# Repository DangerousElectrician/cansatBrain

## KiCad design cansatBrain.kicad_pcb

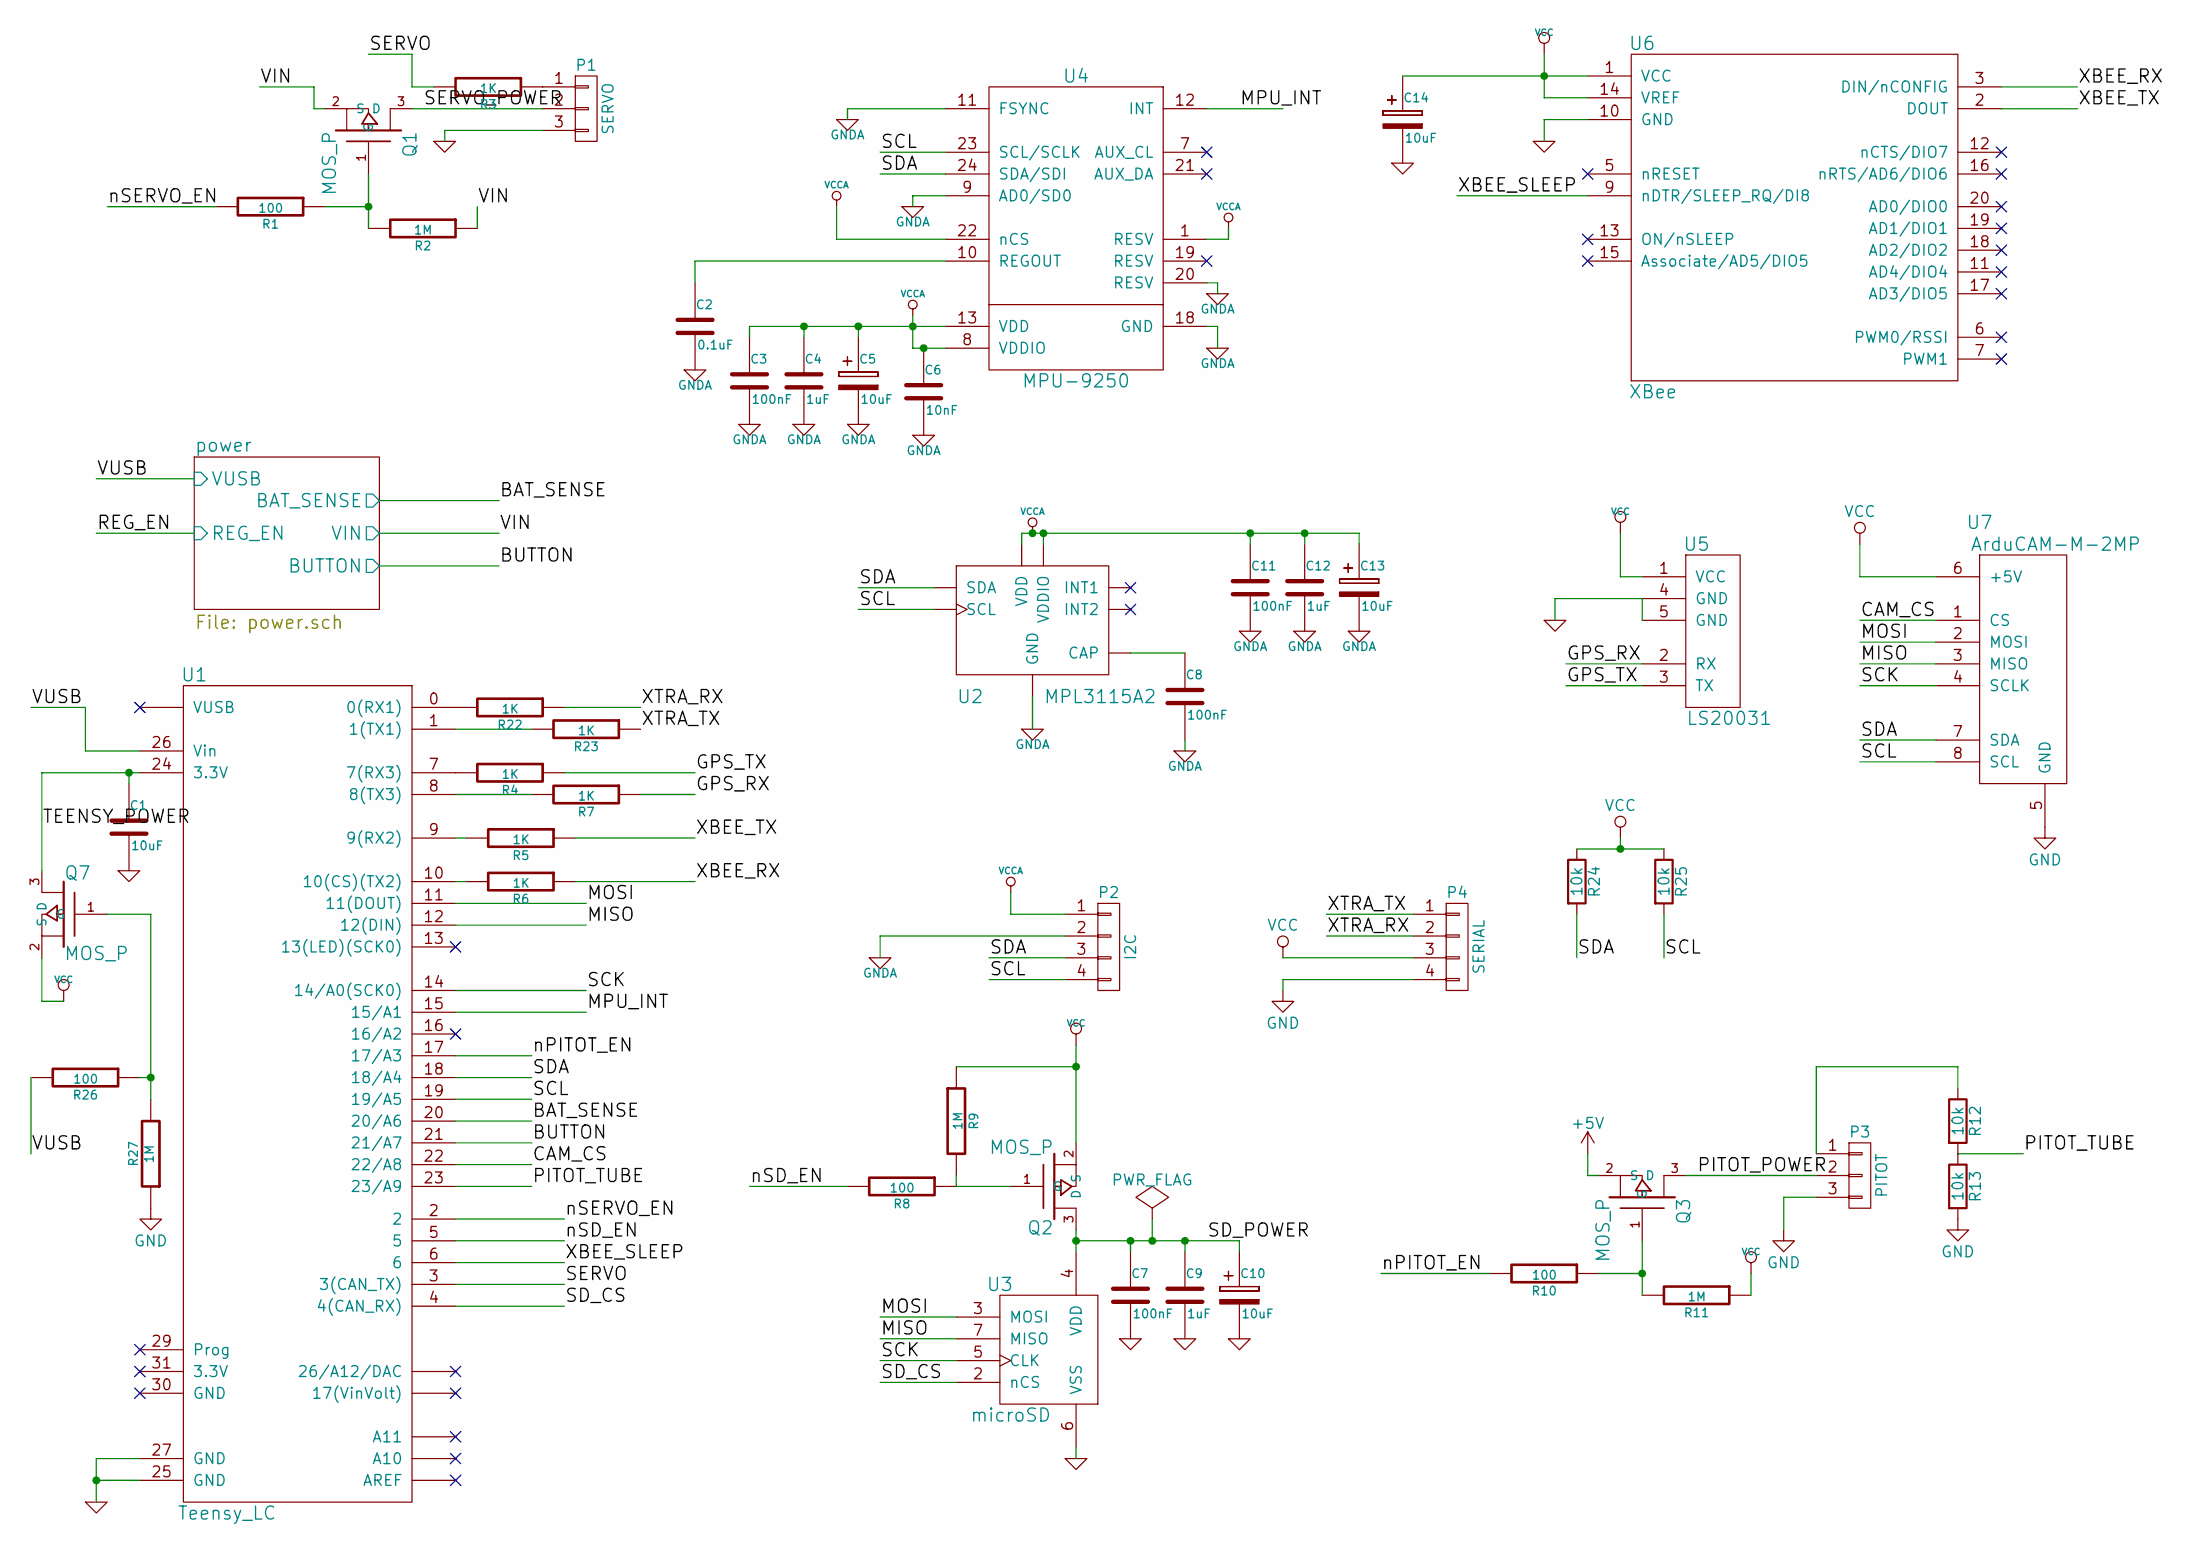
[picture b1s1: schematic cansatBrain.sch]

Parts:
C1, C5, C10, C13, C14: 10uF; C_0805
C2: 0.1uF; C_0402
C3, C7, C8, C11: 100nF; C_0402
C4, C9, C12: 1uF; C_0402
C6: 10nF; C_0402
P1: SERVO; Pin_Header_Straight_1x03
P2: I2C; Pin_Header_Straight_1x04
P3: PITOT; Pin_Header_Straight_1x03
P4: SERIAL; Pin_Header_Straight_1x04
Q1, Q2, Q3, Q7: MOS_P; SOT-23-3
R1, R8, R10, R26: 100; R_0402
R2, R9, R11, R27: 1M; R_0402
R3, R4, R5, R6, R7, R22, R23: 1K; R_0402
R12, R13, R24, R25: 10k; R_0402
U1: Teensy_LC; Teensy_3.1
U2: MPL3115A2; LGA8
U3: microSD; HRS_DM3CS-SF
U4: MPU-9250; QFN-24_3x3MM
U5: LS20031; Pin_Header_Straight_1x05
U6: XBee; xbee
U7: ArduCAM-M-2MP; Pin_Header_Straight_1x08

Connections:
+5V: Q3.2 (S); also elsewhere on the board
/CAM_CS: U1.22 (22/A8), U7.1 (CS)
/GPS_RX: R7.1, U5.2 (RX)
/GPS_TX: R4.1, U5.3 (TX)
/MISO: U1.12 (12(DIN)), U3.7 (MISO), U7.3 (MISO)
/MOSI: U1.11 (11(DOUT)), U3.3 (MOSI), U7.2 (MOSI)
/MPU_INT: U1.15 (15/A1), U4.12 (INT)
/PITOT_POWER: P3.2, Q3.3 (D)
/PITOT_TUBE: R12.2, R13.1, U1.23 (23/A9)
/SCK: U1.14 (14/A0(SCK0)), U3.5 (CLK), U7.4 (SCLK)
/SCL: P2.4, R25.2, U1.19 (19/A5), U2.8 (SCL), U4.23 (SCL/SCLK), U7.8 (SCL)
/SDA: P2.3, R24.2, U1.18 (18/A4), U2.7 (SDA), U4.24 (SDA/SDI), U7.7 (SDA)
/SD_CS: U1.4 (4(CAN_RX)), U3.2 (nCS)
/SD_POWER: C7.1, C9.1, C10.1, Q2.3 (D), U3.4 (VDD)
/SERVO: R3.2, U1.3 (3(CAN_TX))
/SERVO_POWER: P1.2, Q1.3 (D)
/TEENSY_POWER: C1.1, Q7.3 (D), U1.24 (3.3V)
/XBEE_RX: R6.1, U6.3 (DIN/nCONFIG)
/XBEE_SLEEP: U1.6, U6.9 (nDTR/SLEEP_RQ/DI8)
/XBEE_TX: R5.1, U6.2 (DOUT)
/XTRA_RX: P4.2, R22.1
/XTRA_TX: P4.1, R23.1
/nPITOT_EN: R10.2, U1.17 (17/A3)
/nSD_EN: R8.2, U1.5
/nSERVO_EN: R1.2, U1.2
/power/BAT_SENSE: U1.20 (20/A6); also elsewhere on the board
/power/BUTTON: U1.21 (21/A7); also elsewhere on the board
/power/VIN: Q1.2 (S), R2.1; also elsewhere on the board
/power/VUSB: R26.2, U1.26 (Vin); also elsewhere on the board
GND: C1.2, C7.2, C9.2, C10.2, C14.2, P1.3, P3.3, P4.4, R13.2, R27.1, U1.25 (GND), U1.27 (GND), U3.6 (VSS), U5.4 (GND), U5.5 (GND), U6.10 (GND), U7.5 (GND); also elsewhere on the board
GNDA: C2.2, C3.2, C4.2, C5.2, C6.2, C8.2, C11.2, C12.2, C13.2, P2.2, U2.3 (GND), U4.9 (AD0/SD0), U4.11 (FSYNC), U4.18 (GND), U4.20 (RESV); also elsewhere on the board
unnamed: C2.1, U4.10 (REGOUT)
unnamed: C8.1, U2.2 (CAP)
unnamed: P1.1, R3.1
unnamed: P3.1, R12.1
unnamed: Q1.1 (G), R1.1, R2.2
unnamed: Q2.1 (G), R8.1, R9.2
unnamed: Q3.1 (G), R10.1, R11.2
unnamed: Q7.1 (G), R26.1, R27.2
unnamed: R4.2, U1.7 (7(RX3))
unnamed: R5.2, U1.9 (9(RX2))
unnamed: R6.2, U1.10 (10(CS)(TX2))
unnamed: R7.2, U1.8 (8(TX3))
unnamed: R22.2, U1.0 (0(RX1))
unnamed: R23.2, U1.1 (1(TX1))
VCC: C14.1, P4.3, Q2.2 (S), Q7.2 (S), R9.1, R11.1, R24.1, R25.1, U5.1 (VCC), U6.1 (VCC), U6.14 (VREF), U7.6 (+5V); also elsewhere on the board
VCCA: C3.1, C4.1, C5.1, C6.1, C11.1, C12.1, C13.1, P2.1, U2.1 (VDD), U2.4 (VDDIO), U4.1 (RESV), U4.8 (VDDIO), U4.13 (VDD), U4.22 (nCS); also elsewhere on the board

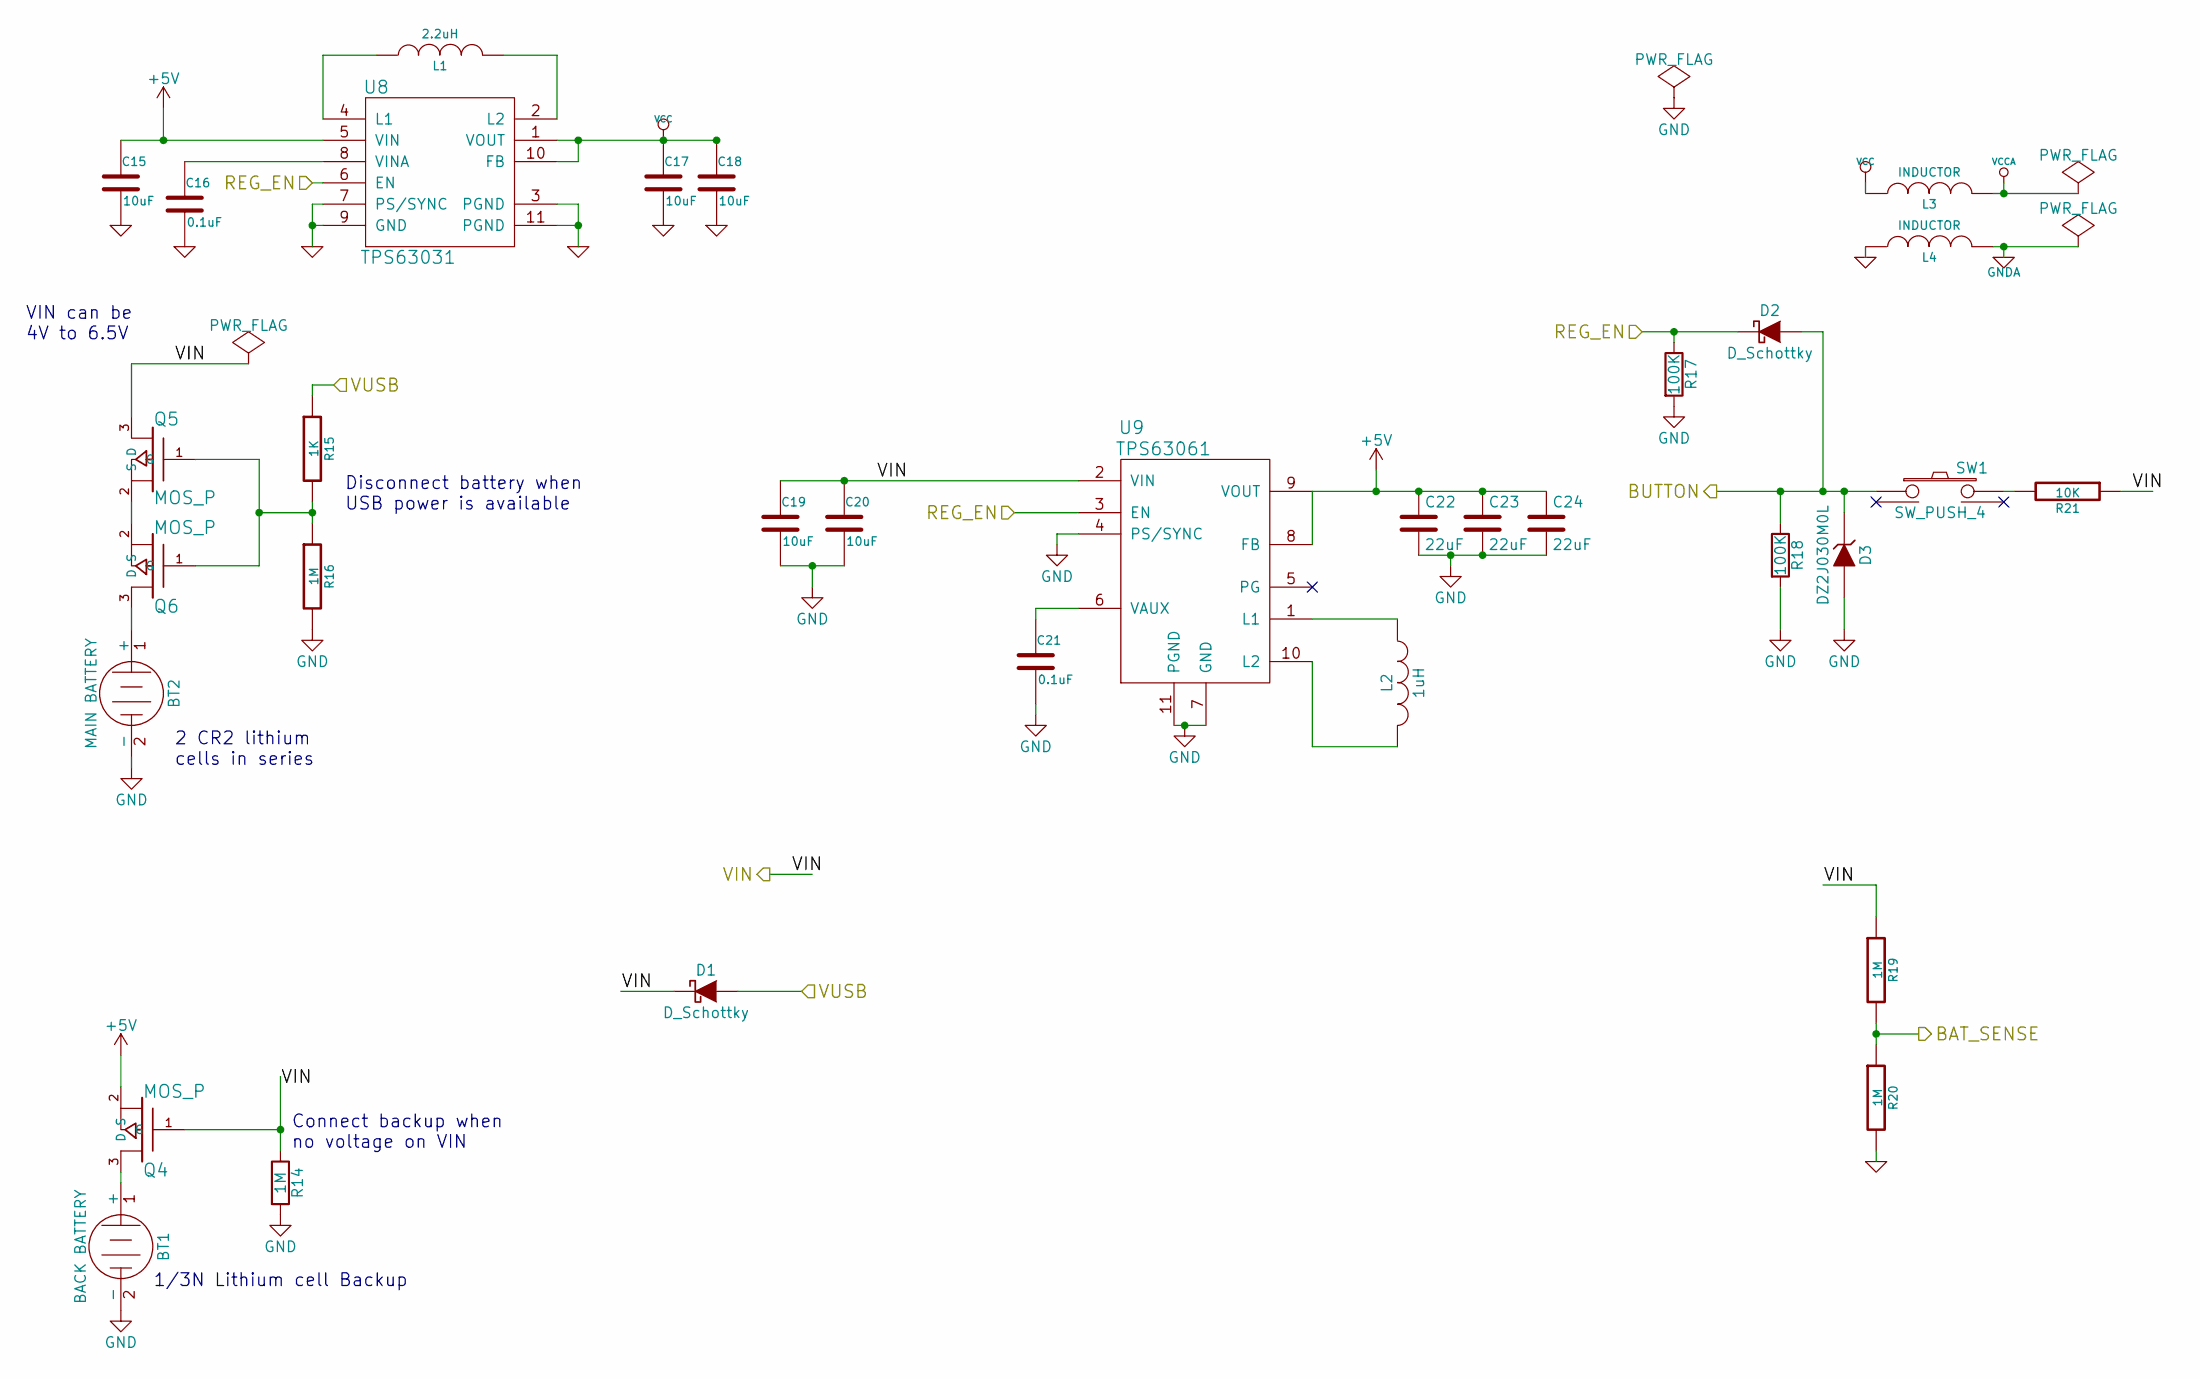
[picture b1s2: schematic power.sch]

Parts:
BT1: BACK BATTERY; BH13N-C
BT2: MAIN BATTERY; Pin_Header_Straight_1x02
C15, C17, C18, C19, C20: 10uF; C_0805
C16, C21: 0.1uF; C_0402
C22, C23, C24: 22uF; C_0805
D1, D2: D_Schottky; SOD-123
D3: DZ2J030M0L; SOD-323
L1: 2.2uH; R_1210
L2: 1uH; SRN4026-1R0Y
L3, L4: INDUCTOR; R_1210
Q4, Q5, Q6: MOS_P; SOT-23-3
R14, R16, R19, R20: 1M; R_0402
R15: 1K; R_0402
R17, R18: 100K; R_0402
R21: 10K; R_0402
SW1: SW_PUSH_4; DIP780W71L599H950Q4
U8: TPS63031; QFN10-2.5MM
U9: TPS63061; WSON-10

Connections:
+5V: C15.1, C22.1, C23.1, C24.1, Q4.2 (S), U8.5 (VIN), U9.8 (FB), U9.9 (VOUT); also elsewhere on the board
/power/BAT_SENSE: R19.2, R20.1; also elsewhere on the board
/power/BUTTON: D2.2 (A), D3.1 (K), R18.1, SW1.1; also elsewhere on the board
/power/REG_EN: D2.1 (K), R17.1, U8.6 (EN), U9.3 (EN)
/power/VIN: C19.1, C20.1, D1.1 (K), Q4.1 (G), Q5.3 (D), R14.1, R19.1, R21.1, U9.2 (VIN); also elsewhere on the board
/power/VUSB: D1.2 (A), R15.1; also elsewhere on the board
GND: BT1.2 (-), BT2.2 (-), C15.2, C16.2, C17.2, C18.2, C19.2, C20.2, C21.2, C22.2, C23.2, C24.2, D3.2 (A), L4.1, R14.2, R16.2, R17.2, R18.2, R20.2, U8.3 (PGND), U8.7 (PS/SYNC), U8.9 (GND), U8.11 (PGND), U9.4 (PS/SYNC), U9.7 (GND), U9.11 (PGND); also elsewhere on the board
GNDA: L4.2; also elsewhere on the board
unnamed: BT1.1 (+), Q4.3 (D)
unnamed: BT2.1 (+), Q6.3 (D)
unnamed: C16.1, U8.8 (VINA)
unnamed: C21.1, U9.6 (VAUX)
unnamed: L1.1, U8.4 (L1)
unnamed: L1.2, U8.2 (L2)
unnamed: L2.1, U9.1 (L1)
unnamed: L2.2, U9.10 (L2)
unnamed: Q5.1 (G), Q6.1 (G), R15.2, R16.1
unnamed: Q5.2 (S), Q6.2 (S)
unnamed: R21.2, SW1.3
VCC: C17.1, C18.1, L3.1, U8.1 (VOUT), U8.10 (FB); also elsewhere on the board
VCCA: L3.2; also elsewhere on the board

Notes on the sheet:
2 CR2 lithium cells in series
Disconnect battery when USB power is available
1/3N Lithium cell Backup
Connect backup when no voltage on VIN
VIN can be 4V to 6.5V

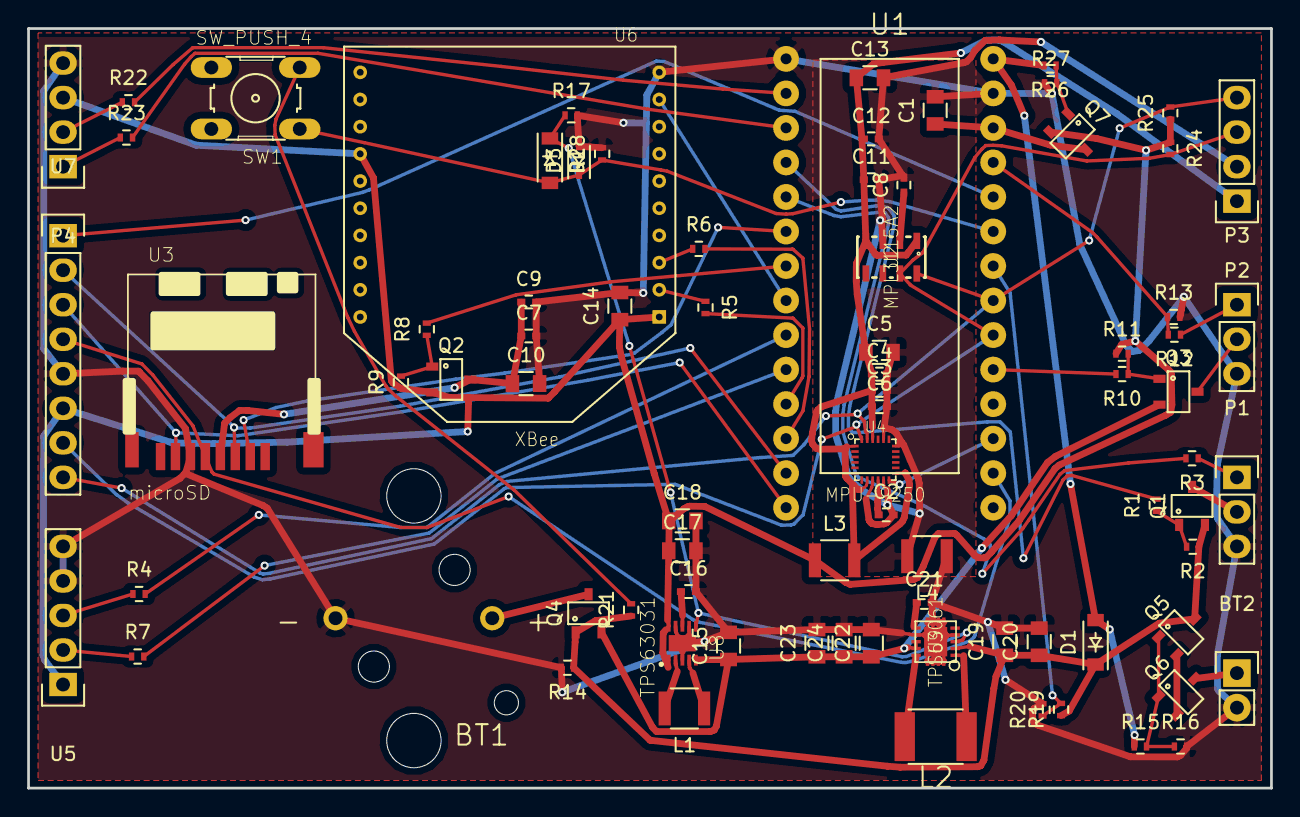
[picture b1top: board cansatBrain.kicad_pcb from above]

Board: 2 copper layers, 91.4 x 55.9 mm, 81 parts (0 on the bottom side), 59 nets.

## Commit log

2015-06-30 stuff
2016-02-29 everything
2016-03-01 ran rescue
2016-03-08 added stuff
2016-03-08 worked on stuff
2016-03-08 added backup battery
2016-03-08 changed button voltage clamp
2016-03-09 increased battery sense resistor values
2016-03-09 added .gitignore
2016-03-09 remove these backup files
2016-03-09 did more work
2016-03-09 more stuff
2016-03-09 footprints
2016-03-09 begin pcb
2016-03-22 a bunch of bom stuff
2016-03-22 ignore temporary and backup files
2016-03-22 some bom files and a library alias file
2016-03-24 laid out board
2016-03-28 ground planes
2016-03-28 files that are readable without kicad
